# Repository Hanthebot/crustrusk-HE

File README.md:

# Crustrusk-HE

Modular, adjustable column-staggered (split) Hall-effect keyboard project

## Disclaimer
- Any layout / designs used in this project that originates from other repositories (e.g. thumb clusters) follows the original author's license.

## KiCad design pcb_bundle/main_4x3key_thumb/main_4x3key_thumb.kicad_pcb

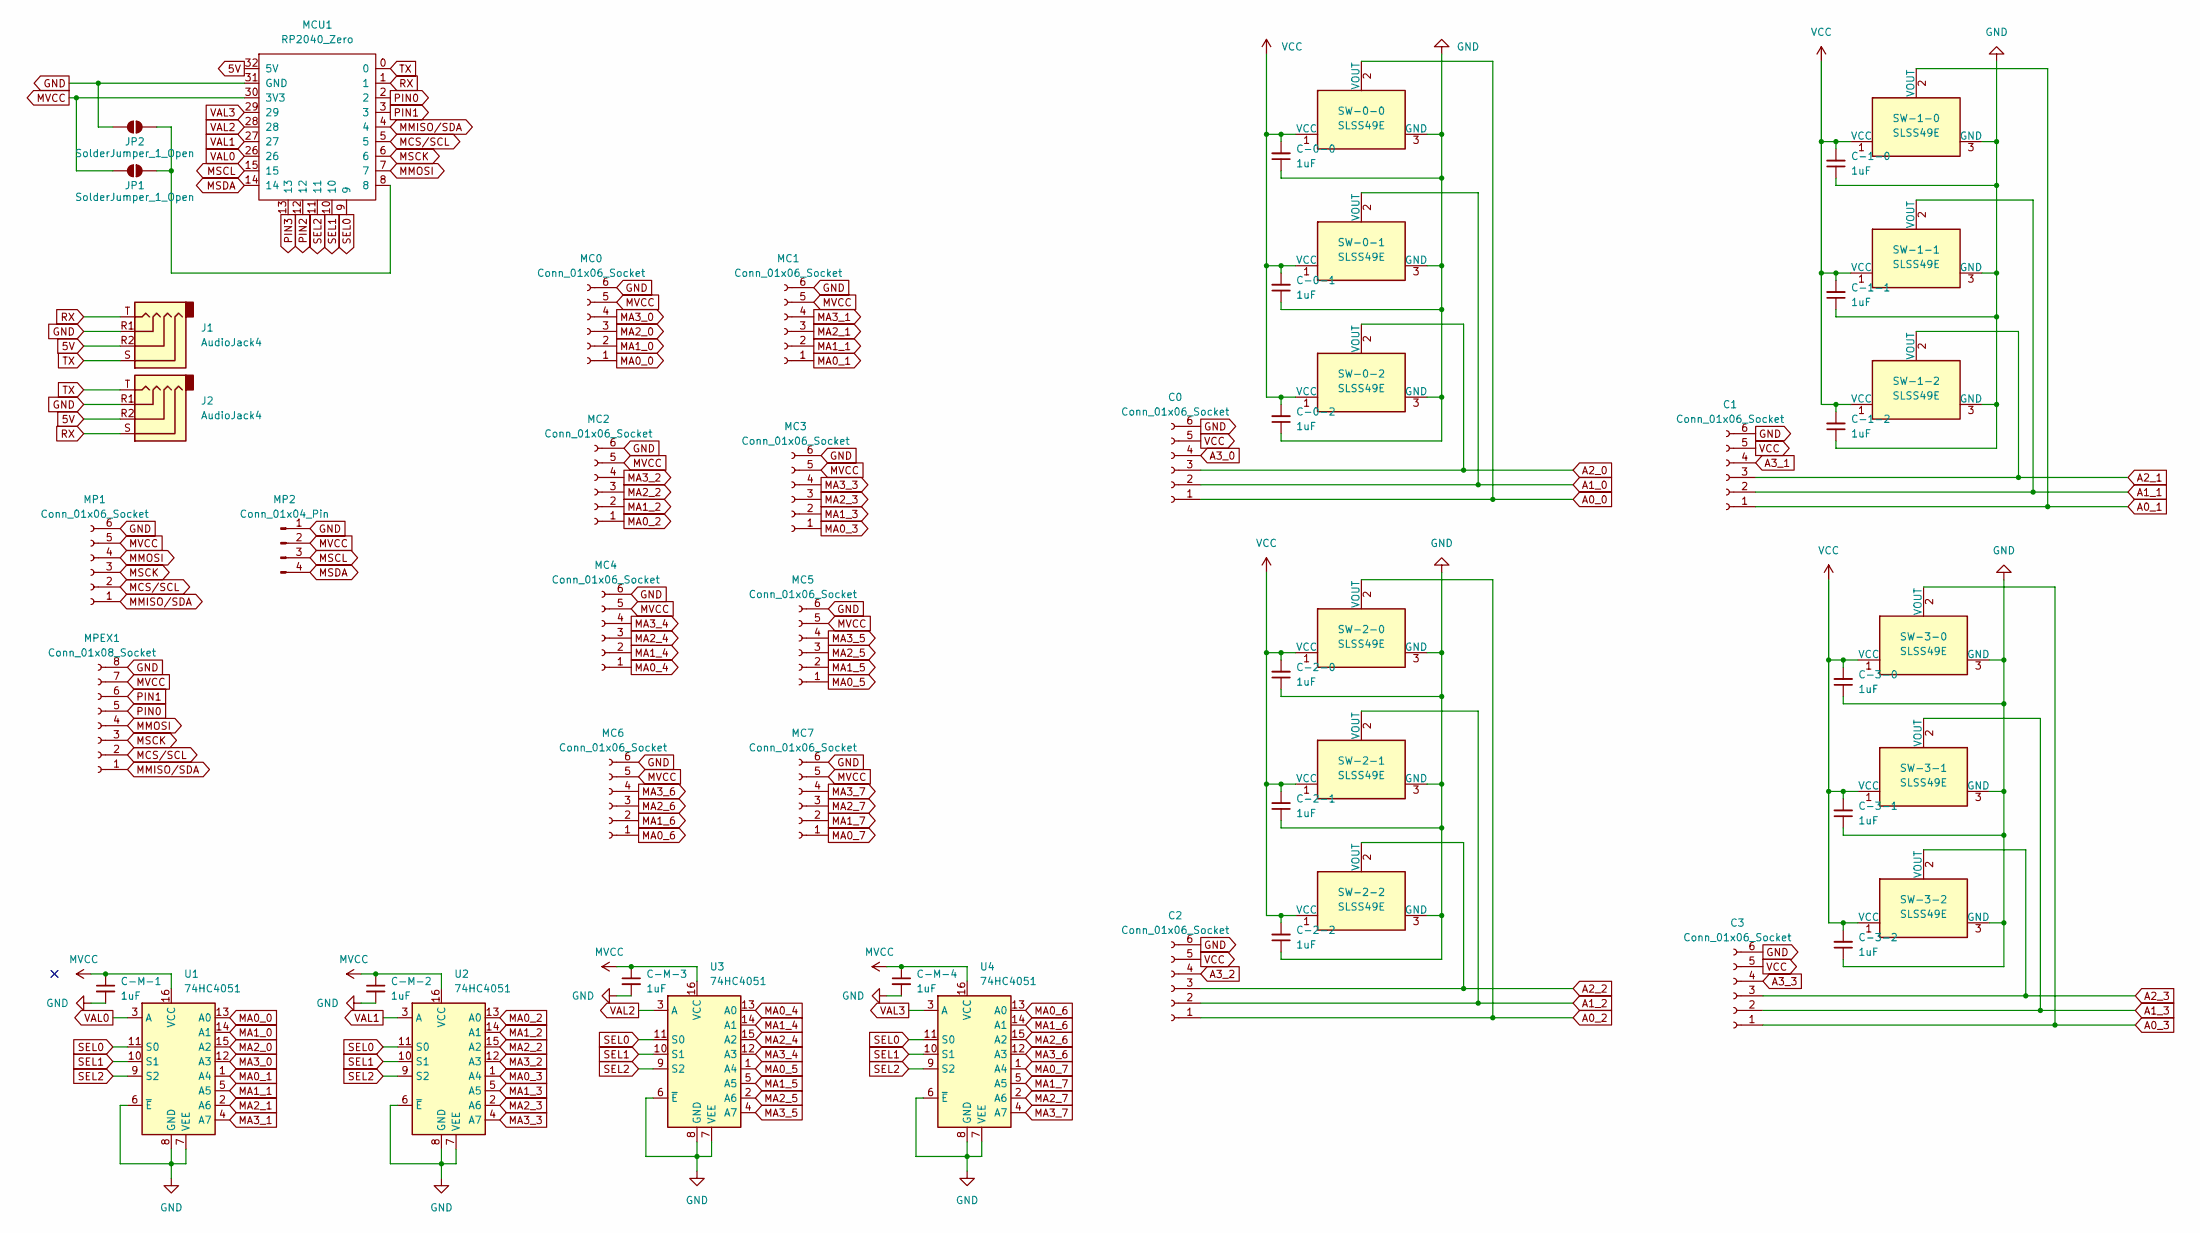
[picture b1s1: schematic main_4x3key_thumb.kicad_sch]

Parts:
C0: Conn_01x06_Socket; reversible JST_PH_S6B-PH-K_1x06_P2.00mm_Horizontal
C1, C2, C3: Conn_01x06_Socket; JST_PH_S6B-PH-K_1x06_P2.00mm_Horizontal
C-0-0, C-0-1, C-0-2: 1uF; C_0805_2012Metric_Pad1.18x1.45mm_HandSolder
C-1-0, C-1-1, C-1-2, C-2-0, C-2-1, C-2-2, C-3-0, C-3-1, C-3-2: 1uF; single_C_0805_2012Metric_Pad1.18x1.45mm_HandSolder
C-M-1, C-M-2, C-M-3, C-M-4: 1uF; single_C_0805_2012Metric_Pad1.18x1.45mm_HandSolder
J1, J2: AudioJack4; TRRS-PJ-320A_PIN
JP1, JP2: SolderJumper_1_Open; SolderJumper-2_P1.3mm_Open_TrianglePad1.0x1.5mm
MC0, MC1, MC2, MC3, MC4, MC5, MC6, MC7: Conn_01x06_Socket; rev_JST_PH_B6B-PH-K_1x06_P2.00mm_Vertical
MCU1: RP2040_Zero; RP2040-Zero-THT-mm
MP1: Conn_01x06_Socket; rev_JST_PH_B6B-PH-K_1x06_P2.00mm_Vertical
MP2: Conn_01x04_Pin; PinHeader_1x04_P1.00mm_Vertical
MPEX1: Conn_01x08_Socket; rev_JST_PH_B8B-PH-K_1x08_P2.00mm_Vertical
SW-0-0, SW-0-1, SW-0-2: SLSS49E; HE-Switch-1U
SW-1-0, SW-1-1, SW-1-2, SW-2-0, SW-2-1, SW-2-2, SW-3-0, SW-3-1, SW-3-2: SLSS49E; single_HE-Switch-1U
U1, U2, U3, U4: 74HC4051; SOIC-16_3.9x9.9mm_P1.27mm

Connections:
5V: J1.R2, J2.R2, MCU1.32 (5V)
A0_0: C0.1, SW-0-0.2 (VOUT)
A0_1: C1.1, SW-1-0.2 (VOUT)
A0_2: C2.1, SW-2-0.2 (VOUT)
A0_3: C3.1, SW-3-0.2 (VOUT)
A1_0: C0.2, SW-0-1.2 (VOUT)
A1_1: C1.2, SW-1-1.2 (VOUT)
A1_2: C2.2, SW-2-1.2 (VOUT)
A1_3: C3.2, SW-3-1.2 (VOUT)
A2_0: C0.3, SW-0-2.2 (VOUT)
A2_1: C1.3, SW-1-2.2 (VOUT)
A2_2: C2.3, SW-2-2.2 (VOUT)
A2_3: C3.3, SW-3-2.2 (VOUT)
A3_0: C0.4
A3_1: C1.4
A3_2: C2.4
A3_3: C3.4
GND: C0.6, C1.6, C2.6, C3.6, C-0-0.1, C-0-1.1, C-0-2.1, C-1-0.1, C-1-1.1, C-1-2.1, C-2-0.1, C-2-1.1, C-2-2.1, C-3-0.1, C-3-1.1, C-3-2.1, C-M-1.2, C-M-2.2, C-M-3.2, C-M-4.2, J1.R1, J2.R1, JP2.1 (A), MC0.6, MC1.6, MC2.6, MC3.6, MC4.6, MC5.6, MC6.6, MC7.6, MCU1.31 (GND), MP1.6, MP2.1, MPEX1.8, SW-0-0.3 (GND), SW-0-1.3 (GND), SW-0-2.3 (GND), SW-1-0.3 (GND), SW-1-1.3 (GND), SW-1-2.3 (GND), SW-2-0.3 (GND), SW-2-1.3 (GND), SW-2-2.3 (GND), SW-3-0.3 (GND), SW-3-1.3 (GND), SW-3-2.3 (GND), U1.6 (~E), U1.7 (VEE), U1.8 (GND), U2.6 (~E), U2.7 (VEE), U2.8 (GND), U3.6 (~E), U3.7 (VEE), U3.8 (GND), U4.6 (~E), U4.7 (VEE), U4.8 (GND)
MA0_0: MC0.1, U1.13 (A0)
MA0_1: MC1.1, U1.1 (A4)
MA0_2: MC2.1, U2.13 (A0)
MA0_3: MC3.1, U2.1 (A4)
MA0_4: MC4.1, U3.13 (A0)
MA0_5: MC5.1, U3.1 (A4)
MA0_6: MC6.1, U4.13 (A0)
MA0_7: MC7.1, U4.1 (A4)
MA1_0: MC0.2, U1.14 (A1)
MA1_1: MC1.2, U1.5 (A5)
MA1_2: MC2.2, U2.14 (A1)
MA1_3: MC3.2, U2.5 (A5)
MA1_4: MC4.2, U3.14 (A1)
MA1_5: MC5.2, U3.5 (A5)
MA1_6: MC6.2, U4.14 (A1)
MA1_7: MC7.2, U4.5 (A5)
MA2_0: MC0.3, U1.15 (A2)
MA2_1: MC1.3, U1.2 (A6)
MA2_2: MC2.3, U2.15 (A2)
MA2_3: MC3.3, U2.2 (A6)
MA2_4: MC4.3, U3.15 (A2)
MA2_5: MC5.3, U3.2 (A6)
MA2_6: MC6.3, U4.15 (A2)
MA2_7: MC7.3, U4.2 (A6)
MA3_0: MC0.4, U1.12 (A3)
MA3_1: MC1.4, U1.4 (A7)
MA3_2: MC2.4, U2.12 (A3)
MA3_3: MC3.4, U2.4 (A7)
MA3_4: MC4.4, U3.12 (A3)
MA3_5: MC5.4, U3.4 (A7)
MA3_6: MC6.4, U4.12 (A3)
MA3_7: MC7.4, U4.4 (A7)
MCS/SCL: MCU1.5, MP1.2, MPEX1.2
MMISO/SDA: MCU1.4, MP1.1, MPEX1.1
MMOSI: MCU1.7, MP1.4, MPEX1.4
MSCK: MCU1.6, MP1.3, MPEX1.3
MSCL: MCU1.15, MP2.3
MSDA: MCU1.14, MP2.4
MVCC: C-M-1.1, C-M-2.1, C-M-3.1, C-M-4.1, JP1.1 (A), MC0.5, MC1.5, MC2.5, MC3.5, MC4.5, MC5.5, MC6.5, MC7.5, MCU1.30 (3V3), MP1.5, MP2.2, MPEX1.7, U1.16 (VCC), U2.16 (VCC), U3.16 (VCC), U4.16 (VCC)
unnamed: JP1.2 (B), JP2.2 (B), MCU1.8
PIN0: MCU1.2, MPEX1.5
PIN1: MCU1.3, MPEX1.6
PIN2: MCU1.12
PIN3: MCU1.13
RX: J1.T, J2.S, MCU1.1
SEL0: MCU1.9, U1.11 (S0), U2.11 (S0), U3.11 (S0), U4.11 (S0)
SEL1: MCU1.10, U1.10 (S1), U2.10 (S1), U3.10 (S1), U4.10 (S1)
SEL2: MCU1.11, U1.9 (S2), U2.9 (S2), U3.9 (S2), U4.9 (S2)
TX: J1.S, J2.T, MCU1.0
VAL0: MCU1.26, U1.3 (A)
VAL1: MCU1.27, U2.3 (A)
VAL2: MCU1.28, U3.3 (A)
VAL3: MCU1.29, U4.3 (A)
VCC: C0.5, C1.5, C2.5, C3.5, C-0-0.2, C-0-1.2, C-0-2.2, C-1-0.2, C-1-1.2, C-1-2.2, C-2-0.2, C-2-1.2, C-2-2.2, C-3-0.2, C-3-1.2, C-3-2.2, SW-0-0.1 (VCC), SW-0-1.1 (VCC), SW-0-2.1 (VCC), SW-1-0.1 (VCC), SW-1-1.1 (VCC), SW-1-2.1 (VCC), SW-2-0.1 (VCC), SW-2-1.1 (VCC), SW-2-2.1 (VCC), SW-3-0.1 (VCC), SW-3-1.1 (VCC), SW-3-2.1 (VCC)

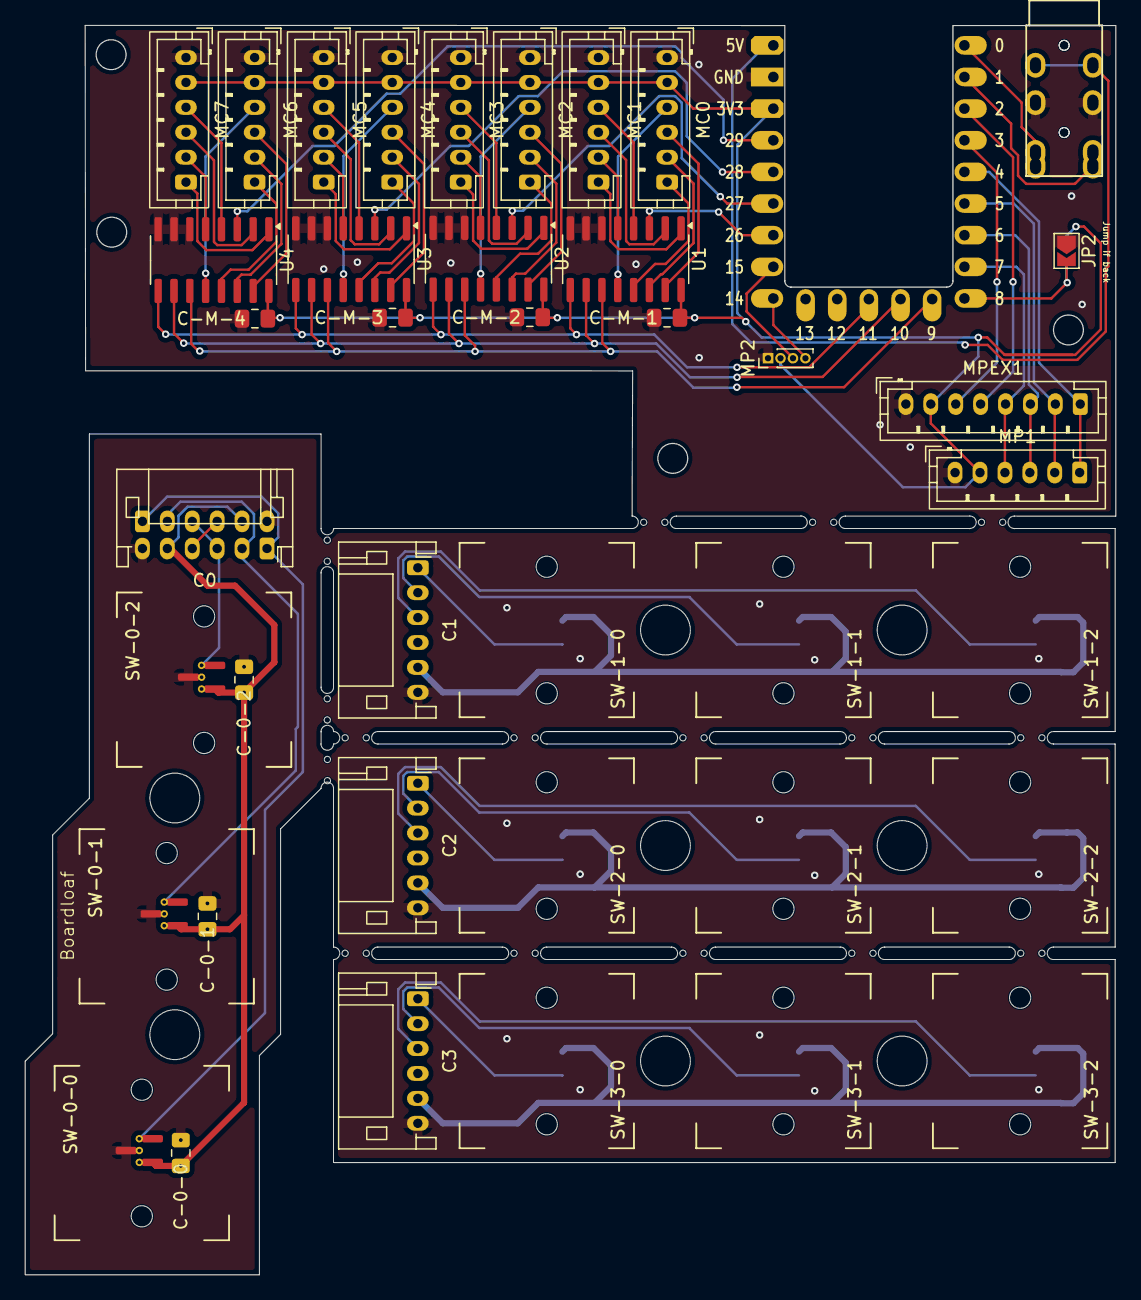
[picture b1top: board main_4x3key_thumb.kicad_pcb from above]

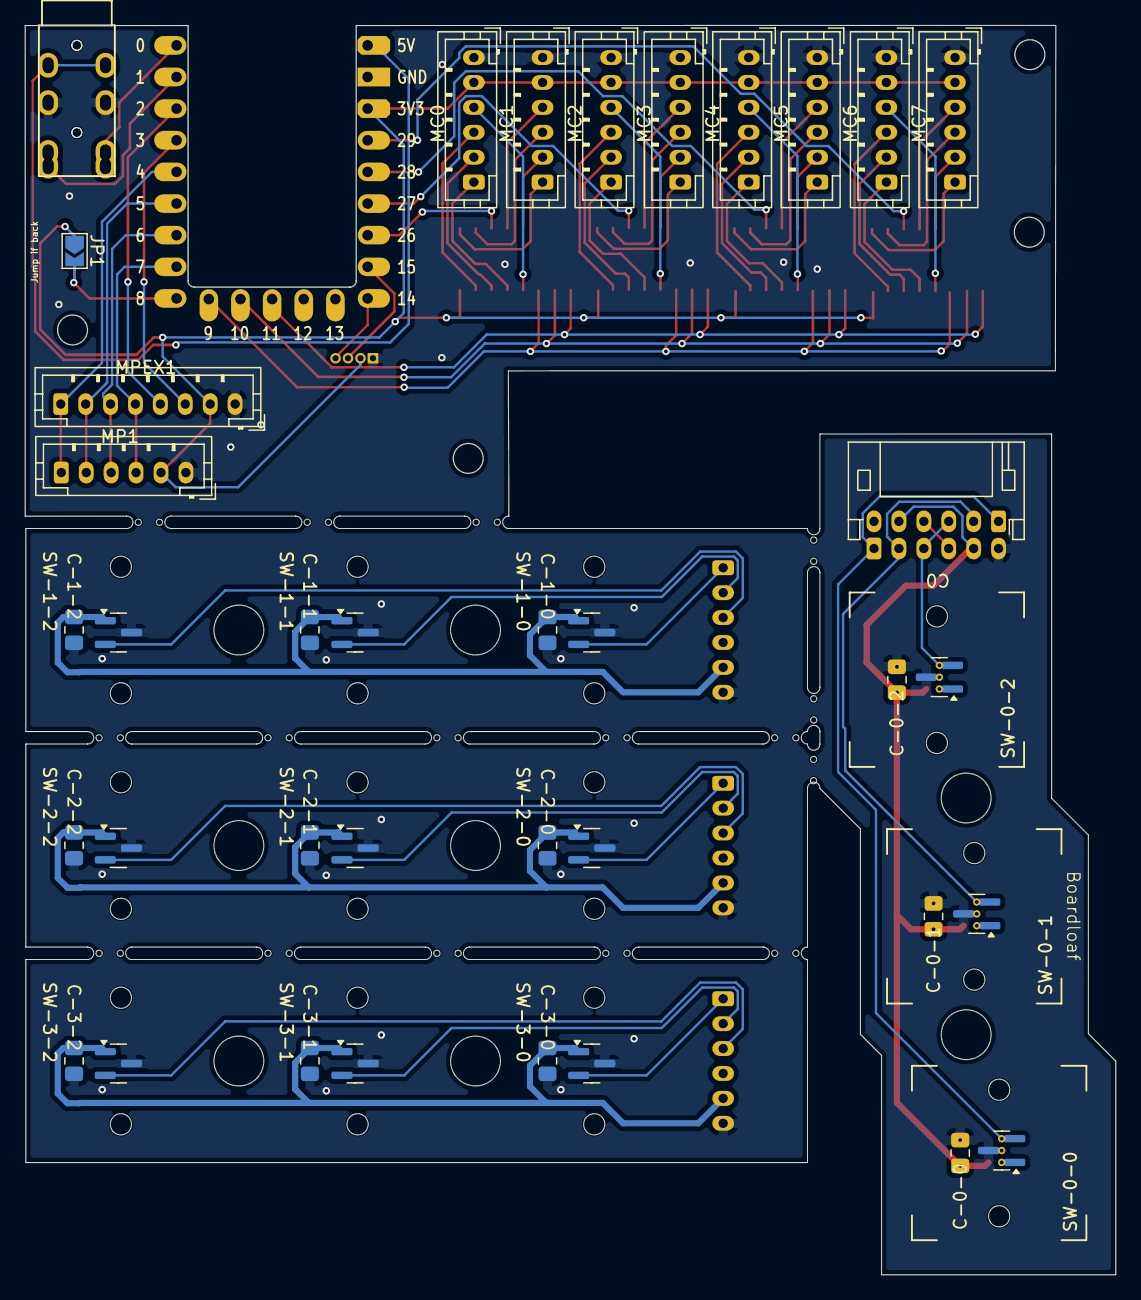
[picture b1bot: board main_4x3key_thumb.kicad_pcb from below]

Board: 2 copper layers, 87.5 x 100.3 mm, 56 parts (11 on the bottom side), 66 nets.

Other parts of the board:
Ref**: Val**; hole-m2-screw
Ref**#2, Ref**#3, Ref**#4: Val**; hole-m2-screw
